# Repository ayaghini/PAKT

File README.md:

# PAKT

## Executive Summary
PAKT is an ESP32-S3-based APRS pocket TNC/tracker built around an SA818 VHF radio,
SGTL5000 audio codec, GPS, and BLE. The MVP now includes both the native PAKT BLE
protocol and KISS-over-BLE so existing APRS software can use the device as a BLE TNC.

The software foundation is substantially in place, and the current bench prototype
has now cleared the core codec and radio bring-up steps:
- firmware includes AX.25/APRS framing, AFSK modulator/demodulator, BLE GATT services,
  KISS-over-BLE, APRS TX scheduling, telemetry payloads, SGTL5000 audio pipeline bring-up,
  staged SA818 bench tests, and SA818 control paths
- the desktop test app and KISS bridge are implemented as reference host tools
- an in-repo iPhone-only SwiftUI app track now exists under `app/ios/`, built against the same native BLE protocol as the desktop client
- host-side software evidence is strong, with current docs recording `364/364` host tests passing
- bench bring-up has confirmed SGTL5000 discovery and headphone output, shared I2C
  visibility for the MAX17048 and M9N, SA818 UART handshake/config, staged PTT/audio tests,
  and short APRS packet TX receipt on a separate receiver

Recent bench work materially improved the RF picture:
- SA818 UART handshake/config recovered and is now responding again on hardware
- staged PTT test and 10-tone TX bench are confirmed working on the current prototype
- APRS packet TX is now bench-proven again on the current hardware state, with packets
  received externally during the restored full test flow
- RX analog/audio activity reaches the demodulator and now has stronger instrumentation
- RX debug now includes PSRAM-backed WAV export, selectable bench stages, selectable
  sample-path conditioning, and a `16 kHz` capture mode
- a separate quiet-capture firmware profile now supports repeated `30 s` low-noise
  captures with a countdown and framed binary export suitable for handoff analysis
- on-device APRS RX is now proven on hardware after fixing a half-rate I2S capture bug
  and reducing Stage C SA818 receive volume; the prototype now decodes APRS frames on-device
- the APRS message-ack path is now wired into `TxScheduler`, so on-air APRS acks
  can complete the firmware message FSM instead of always timing out
- the GPS path now prefers the shared Feather I2C/STEMMA bus (`u-blox M9N @ 0x42`)
  with `UART2` (`GPIO17/GPIO18`, `38400` baud) retained as a fallback; raw NMEA
  traffic is now logged/published even before a valid fix
- GPS over the shared Feather I2C/STEMMA bus is now working on the current
  prototype, including live telemetry delivery to the app; this path should now
  be treated as the default GPS integration baseline rather than an open bring-up item

The project is not MVP-complete yet because hardware validation still gates the milestone:
- BLE security and PTT fail-safe validation on hardware
- SA818 deviation and on-air receive/transmit calibration
- trusted Bell 202 source validation and on-device APRS RX proof
- third-party KISS client validation

## Project Status At A Glance

| Area | Status | Notes |
|---|---|---|
| Core firmware architecture | `strong` | AX.25/APRS, AFSK, BLE, KISS-over-BLE, scheduling, and host tooling are implemented |
| Bench bring-up | `in progress` | I2C, codec bring-up, SA818 UART/config, PTT, staged TX audio, and APRS TX bench are working |
| APRS TX over RF | `proven on current prototype` | tone sequence and APRS packets were heard/received again after SA818 recovery on 2026-03-21 |
| APRS RX over RF | `proven on current prototype` | quiet-profile RX now decodes APRS on-device after fixing the half-rate capture bug and reducing Stage C volume |
| BLE/KISS hardware validation | `pending` | software-complete enough for hardware validation |
| GPS over shared I2C | `proven on current prototype` | `u-blox M9N @ 0x42` is detected after startup, hot-switches to I2C/DDC, and publishes live telemetry to the app |
| MVP milestone | `open` | blocked by BLE safety validation, radio calibration/repeatability, and remaining hardware gates

## Progress Summary
- Software stack is largely implemented and test-backed.
- Prototype hardware can boot the codec/radio path, recover SA818 control, transmit APRS packets over RF, and now decode APRS on-device.
- Main firmware is now in production mode by default: recorder/export bench stages are disabled on boot while the continuous APRS RX path remains active.
- Demodulator instrumentation now exposes RX peak, flag, FCS-reject, and decode counters during bench work.
- Bench stages are now selectable through [bench_profile_config.h](/Users/macmini4/Desktop/PAKT/firmware/main/bench_profile_config.h), so debug sessions can run only the needed benches/stages instead of the full boot-time sequence.
- Full RX recorder/export now works through PSRAM-backed WAV capture, and the quiet profile can export captured demod-input audio through a framed binary serial stream for offline reconstruction.
- A real RX blocker was found and fixed: the audio pipeline was unpacking only half of each 2048-byte I2S read, effectively feeding the demodulator at `8 kHz` while configured for `16 kHz`.
- After fixing that bug and lowering quiet-profile Stage C SA818 volume from `8` to `4`, the device decoded multiple on-air APRS frames in the same `30 s` window.
- GPS parsing is no longer a stub: `gps_task` now reads the M9N over the shared I2C bus when present, falls back to UART if needed, and publishes BLE GPS telemetry even in the no-fix state.
- GPS over the shared Feather I2C/STEMMA bus is now confirmed working in the current hardware setup, and live GPS data is reaching the app.
- APRS ack handling is no longer a dead end: received APRS acks can now call `ctx.notify_ack()` and complete the message FSM in firmware.
- The RX path is now also configurable at the firmware level for:
  - `8 kHz` or `16 kHz` audio rate
  - left/right/average/stronger channel selection
  - stereo-slot swap
  - sample byte swap
  - firmware DC blocking
- The current best debugging workflow is the separate quiet-capture profile.
- The repo now distinguishes clearly between:
  - audio-path alive
  - packet TX proven
  - on-device APRS RX now proven on the corrected quiet profile

## Immediate Next Steps
1. Validate BLE encrypted+bonded write enforcement and PTT fail-safe behavior on live hardware.
2. Verify the newly wired APRS ack path end-to-end with real on-air message acknowledgements.
3. Validate native BLE + KISS-over-BLE behavior on hardware, including reconnect and at least one real client path.
4. Bring up the iPhone app against the same firmware build: connect, view APRS RX/GPS/status, send TX requests, change radio settings, and enable the BLE debug stream.
5. Keep the shared-I2C GPS path as the default baseline and only use UART fallback for alternate wiring or recovery.

## Bench Profile
- Bench/debug stage selection is controlled in [bench_profile_config.h](/Users/macmini4/Desktop/PAKT/firmware/main/bench_profile_config.h).
- Current toggles allow independent enable/disable of:
  - `audio_bench`
  - `sa818_bench`
  - `aprs_bench`
  - APRS Stage 0 loopback
  - APRS Stage A TX burst
  - APRS Stage B RX gain sweep
  - APRS PCM snapshot dump
  - APRS Stage C full RX recorder/export
- Stage C also has a selectable ADC gain step so targeted RX captures can be taken at the most useful receive setting.
- The same file now controls the audio debug sample rate and RX sample interpretation path.

## Current Status
- Phase: prototype hardware bring-up in progress, with packet TX, on-device APRS RX, and shared-I2C GPS telemetry now proven on the current prototype; remaining work is calibration, repeatability, app validation, and safety validation
- Firmware build flow: ESP-IDF with `idf.py`
- Host test flow: raw CMake only for `firmware/test_host`
- Canonical wire-format source: `docs/aprs_mvp_docs/payload_contracts.md`
- Canonical implementation/risk ledger: `docs/aprs_mvp_docs/agent_bootstrap/audit.md`

## Bench-Proven Baseline
- Feather target: Adafruit ESP32-S3 Feather `4 MB flash / 2 MB PSRAM`
- Shared I2C bus: `SGTL5000 @ 0x0A`, `MAX17048 @ 0x36`, `u-blox M9N @ 0x42`
- Audio bring-up rule: enable `SYS_MCLK` before SGTL5000 I2C init
- Verified audio wiring:
  - `GPIO3` `I2C_SDA`
  - `GPIO4` `I2C_SCL`
  - `GPIO8` `I2S_BCLK`
  - `GPIO15` `I2S_WS`
  - `GPIO12` `I2S_DOUT`
  - `GPIO10` `I2S_DIN`
  - `GPIO14` `I2S_MCLK`
- Verified radio control wiring:
  - `GPIO13` `SA818_RX_CTRL`
  - `GPIO9` `SA818_TX_STAT`
  - `GPIO11` `SA818_PTT`
- Restored and re-verified on 2026-03-21:
  - `AT+DMOCONNECT` handshake passes
  - `AT+DMOSETGROUP` frequency config passes
  - staged PTT test passes
  - 10-tone TX bench is audible on a receiver
  - APRS packet TX is received externally
- Bench modules now in the firmware tree:
  - `firmware/main/audio_bench_test/`
  - `firmware/main/sa818_bench_test/`

## Next Steps
- Measure TX deviation and formalize the corrected RX baseline in the bench docs
- Re-run APRS RX across multiple sessions to confirm repeatable decode margin on the corrected quiet profile
- If needed, tune SGTL5000 input/gain/sample interpretation using the new sample-path debug controls, but the core on-device RX proof now exists
- Measure and record SA818 TX deviation with the actual `LINE_OUT -> AF_IN` attenuation in place
- Validate BLE security enforcement and PTT watchdog behavior on the live hardware stack
- Freeze the harness values into the PCB-facing docs once AF levels, deviation, and PTT topology are measured

## Start Here
- `docs/README.md`
- `docs/aprs_mvp_docs/README.md`
- `docs/aprs_mvp_docs/agent_bootstrap/README.md`
- `docs/aprs_mvp_docs/agent_bootstrap/implementation_steps_mvp.md`
- `docs/aprs_mvp_docs/agent_bootstrap/gate_pass_matrix.md`
- `docs/aprs_mvp_docs/agent_bootstrap/audit.md`
- `docs/aprs_mvp_docs/docs/02_mvp_scope.md`
- `docs/aprs_mvp_docs/docs/05_ble_gatt_spec.md`
- `docs/aprs_mvp_docs/docs/19_ble_integration_reference.md`
- `docs/aprs_mvp_docs/docs/16_kiss_over_ble_spec.md`
- `docs/aprs_mvp_docs/payload_contracts.md`
- `docs/dev_setup.md`
- `docs/bench_bringup_checklist.md`
- `hardware/prototyping_wiring.md`
- `hardware/prototype_breakout_wiring_plan.md`

## Repository Layout
- `docs/`: unified documentation home
- `firmware/`: ESP-IDF firmware, host tests, and embedded integration code
- `app/desktop_test/`: desktop BLE reference client and KISS bridge/harness
- `docs/aprs_mvp_docs/docs/`: product, architecture, protocol, firmware, test, and risk docs
- `docs/aprs_mvp_docs/agent_bootstrap/`: low-token onboarding pack, implementation sequence, gates, and audit log
- `docs/aprs_mvp_docs/hardware/`: hardware interface notes and placeholder BOM
- `docs/hardware/`: hardware source library, CAD asset tracking, and reference links
- `docs/dev_setup.md` + `docs/bench_bringup_checklist.md`: operator/developer companion docs
- `hardware/`: practical prototyping wiring and hardware rationale
- `handoff/agent_integration_package/`: external-agent handoff package for host-software integration work

## Working Rules
- Use ESP-IDF `idf.py` for firmware builds; do not use raw CMake as the direct firmware entrypoint.
- Use raw CMake only for pure-software host tests under `firmware/test_host`.
- Keep `docs/aprs_mvp_docs/docs/05_ble_gatt_spec.md`,
- `docs/aprs_mvp_docs/docs/19_ble_integration_reference.md`,
- `docs/aprs_mvp_docs/agent_bootstrap/ble_protocol_quickref.md`,
  `docs/aprs_mvp_docs/docs/16_kiss_over_ble_spec.md`, and
  `docs/aprs_mvp_docs/payload_contracts.md` aligned with the implementation.
- If BLE UUIDs, payload fields, command semantics, chunking, or client behavior changes,
  update all relevant protocol docs in the same change so the desktop app, iPhone app,
  firmware, and future integrations do not drift.
- Prefer `firmware/main/main.cpp` and the component implementations as the source of truth for what is actually wired versus still hardware-gated.

## Build Directories
- `firmware/build_*` are the intended build output directories for the firmware project.
- Repo-root `build_feather_s3/` is also an ESP-IDF-generated build tree for the same `firmware/` project, not a second source tree.
- The metadata inside both `build_feather_s3/project_description.json` and `firmware/build_feather_s3/project_description.json` points back to `firmware/`; the difference is only the chosen build output path.

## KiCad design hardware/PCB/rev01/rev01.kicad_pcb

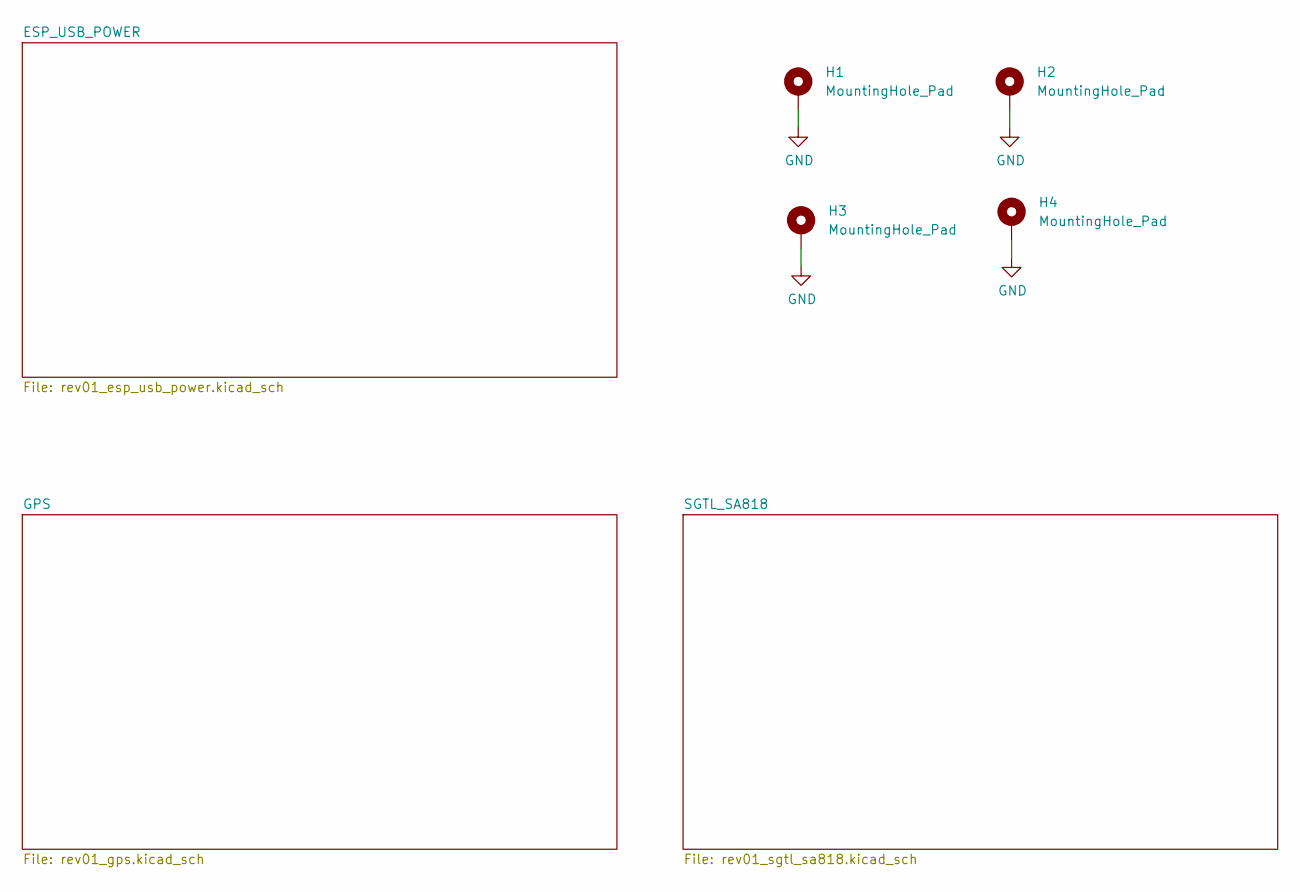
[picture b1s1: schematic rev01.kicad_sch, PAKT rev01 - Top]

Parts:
H1, H2, H3, H4: MountingHole_Pad; MountingHole_3.2mm_M3_Pad

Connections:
GND: H1.1, H2.1, H3.1, H4.1; also elsewhere on the board

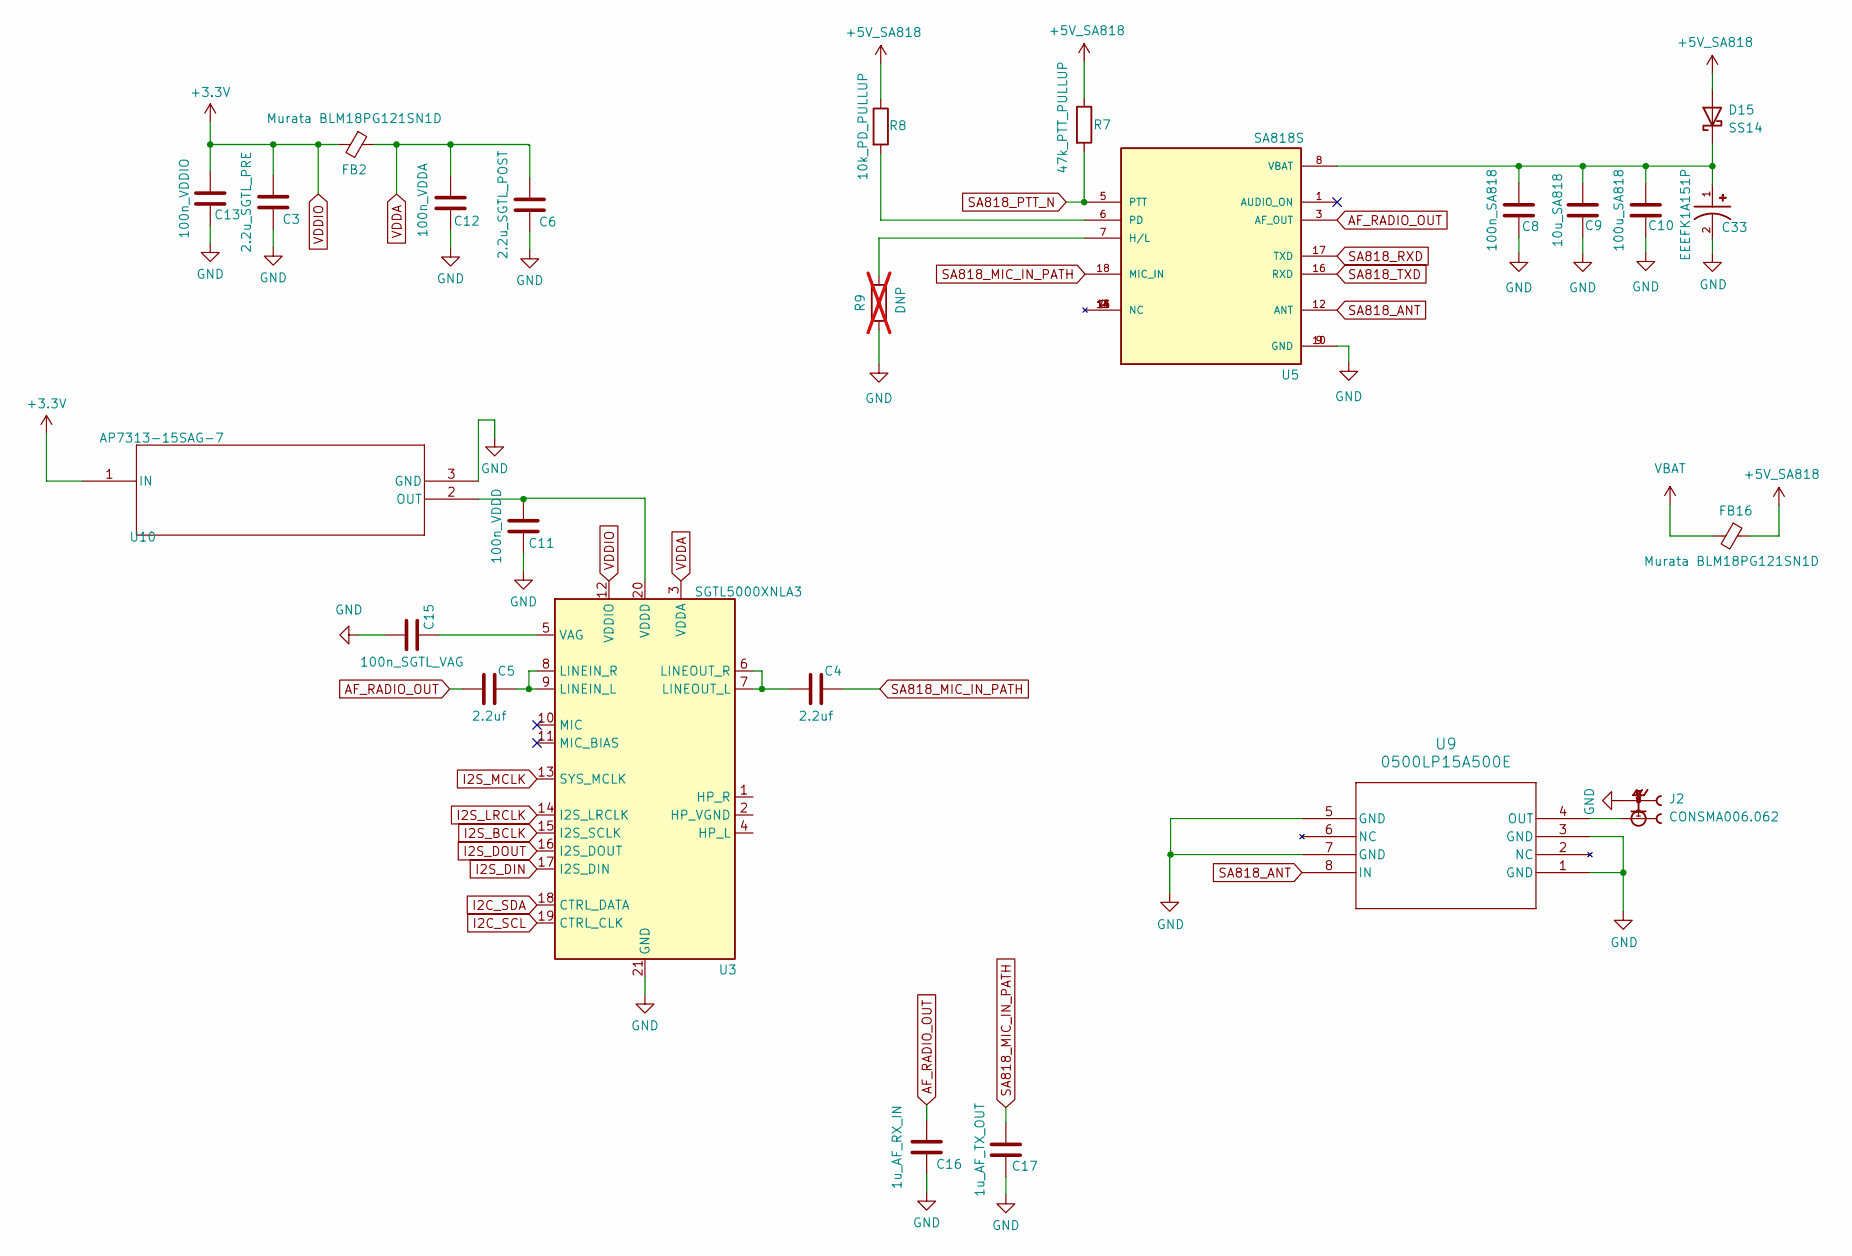
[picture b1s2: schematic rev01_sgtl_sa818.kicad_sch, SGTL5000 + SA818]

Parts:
C3: 2.2u_SGTL_PRE; C_0603_1608Metric
C4, C5: 2.2uf; C_0603_1608Metric
C6: 2.2u_SGTL_POST; C_0603_1608Metric
C8: 100n_SA818; C_0603_1608Metric
C9: 10u_SA818; C_0805_2012Metric
C10: 100u_SA818; C_1206_3216Metric
C11: 100n_VDDD; C_0603_1608Metric
C12: 100n_VDDA; C_0603_1608Metric
C13: 100n_VDDIO; C_0603_1608Metric
C15: 100n_SGTL_VAG; C_0603_1608Metric
C16: 1u_AF_RX_IN; C_0603_1608Metric
C17: 1u_AF_TX_OUT; C_0603_1608Metric
C33: EEEFK1A151P; CAP_EEEFK1A151P; PARTREV 10-Oct-19
D15: SS14; D_SMA; MPN SS14
FB2, FB16: Murata BLM18PG121SN1D; R_0603_1608Metric; MPN BLM18PG121SN1D
J2: CONSMA006.062; SMA_Amphenol_132134-14_Vertical_P5; PARTREV B
R7: 47k_PTT_PULLUP; R_0603_1608Metric
R8: 10k_PD_PULLUP; R_0603_1608Metric
R9: DNP; R_0603_1608Metric; not fitted
U3: SGTL5000XNLA3; HUQFN20_SOT1628-1_NXP
U5: SA818S; XCVR_SA818S
U9: 0500LP15A500E; 0500LP15A500E_JOT; MPN 0500LP15A500E
U10: AP7313-15SAG-7; AP7313_15SAG_7

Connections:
+5V_SA818: D15.2 (A), FB16.1, R7.1, R8.1
AF_RADIO_OUT: C5.1, C16.1, U5.3 (AF_OUT)
GND: C3.2, C6.2, C8.2, C9.2, C10.2, C11.2, C12.2, C13.2, C15.1, C16.2, C17.2, C33.2, J2.2, J2.3, J2.4, J2.5, R9.1, U3.21 (GND), U5.9 (GND), U5.10 (GND), U9.1 (GND), U9.3 (GND), U9.5 (GND), U9.7 (GND), U10.3 (GND); also elsewhere on the board
I2C_SCL: U3.19 (CTRL_CLK); also elsewhere on the board
I2C_SDA: U3.18 (CTRL_DATA); also elsewhere on the board
I2S_BCLK: U3.15 (I2S_SCLK); also elsewhere on the board
I2S_DIN: U3.17 (I2S_DIN); also elsewhere on the board
I2S_DOUT: U3.16 (I2S_DOUT); also elsewhere on the board
I2S_LRCLK: U3.14 (I2S_LRCLK); also elsewhere on the board
I2S_MCLK: U3.13 (SYS_MCLK); also elsewhere on the board
unnamed: C8.1, C9.1, C10.1, C33.1, D15.1 (K), U5.8 (VBAT)
unnamed: C5.2, U3.8 (LINEIN_R), U3.9 (LINEIN_L)
unnamed: C4.1, U3.6 (LINEOUT_R), U3.7 (LINEOUT_L)
unnamed: C15.2, U3.5 (VAG)
unnamed: R9.2, U5.7 (H/L)
unnamed: R8.2, U5.6 (PD)
unnamed: J2.1, U9.4 (OUT)
unnamed: C11.1, U3.20 (VDDD), U10.2 (OUT)
SA818_ANT: U5.12 (ANT), U9.8 (IN)
SA818_MIC_IN_PATH: C4.2, C17.1, U5.18 (MIC_IN)
SA818_PTT_N: R7.2, U5.5 (PTT); also elsewhere on the board
SA818_RXD: U5.17 (TXD); also elsewhere on the board
SA818_TXD: U5.16 (RXD); also elsewhere on the board
VBAT: FB16.2; also elsewhere on the board
VDDA: C6.1, C12.1, FB2.1, U3.3 (VDDA)
VDDIO: C3.1, C13.1, FB2.2, U3.12 (VDDIO), U10.1 (IN); also elsewhere on the board

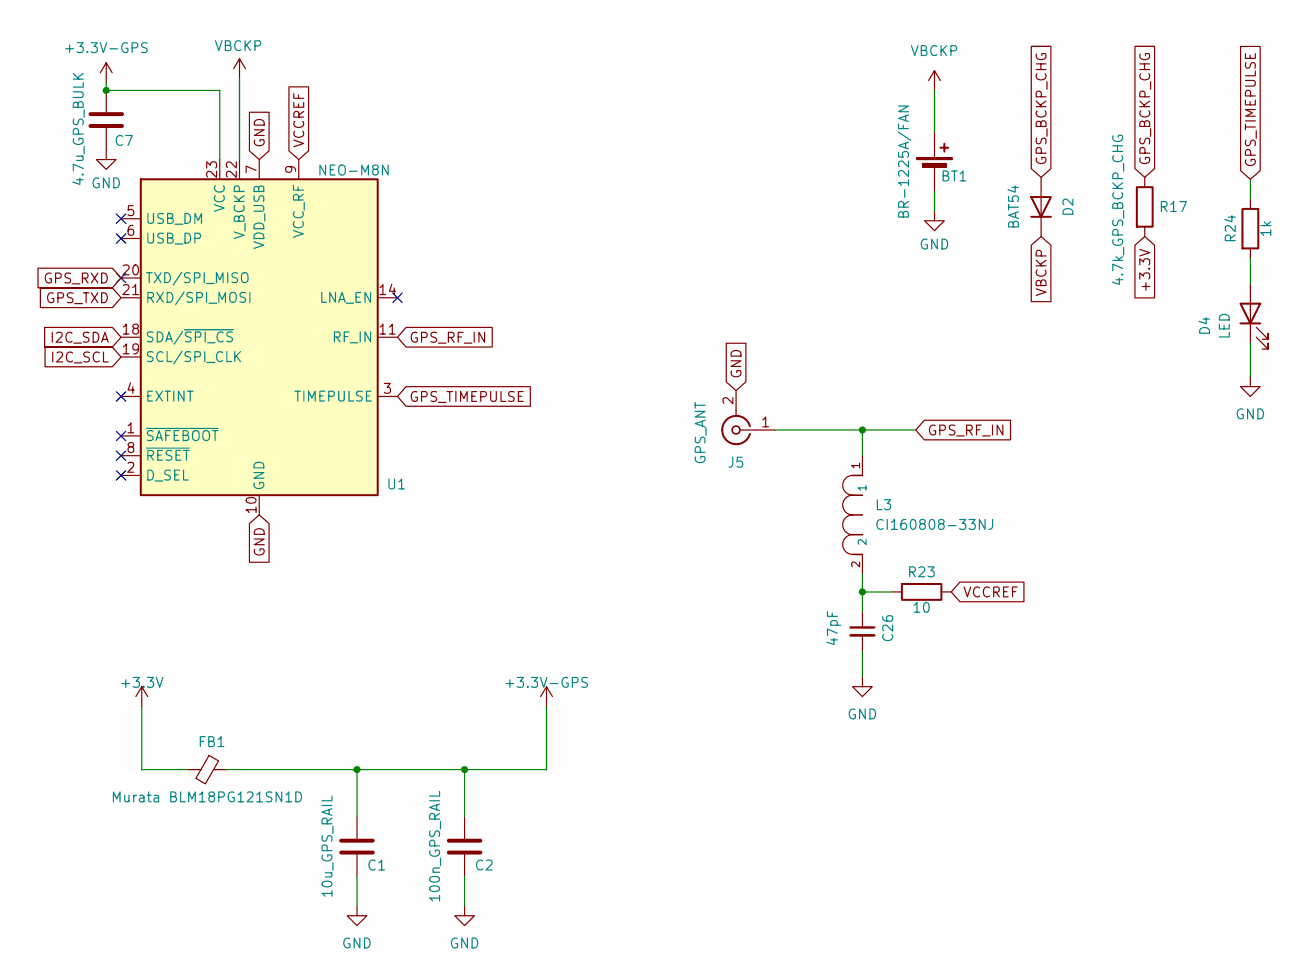
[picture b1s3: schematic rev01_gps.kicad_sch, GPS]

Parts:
BT1: BR-1225A/FAN; BatteryHolder_Keystone_3000_1x12mm
C1: 10u_GPS_RAIL; C_0805_2012Metric
C2: 100n_GPS_RAIL; C_0603_1608Metric
C7: 4.7u_GPS_BULK; C_0805_2012Metric
C26: 47pF; C_0402_1005Metric
D2: BAT54; D_SOD-323
D4: LED; LED_0603_1608Metric
FB1: Murata BLM18PG121SN1D; R_0603_1608Metric; MPN BLM18PG121SN1D
J5: GPS_ANT; U.FL_Hirose_U.FL-R-SMT-1_Vertical
L3: CI160808-33NJ; L_0603_1608Metric; TOLERANCE ±5 %; MPN CI160808-33NJ
R17: 4.7k_GPS_BCKP_CHG; R_0603_1608Metric
R23: 10; R_0603_1608Metric
R24: 1k; R_0603_1608Metric
U1: NEO-M8N; ublox_NEO

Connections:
+3.3V-GPS: C1.1, C2.1, C7.1, FB1.1, U1.23 (VCC)
GND: BT1.2 (-), C1.2, C2.2, C7.2, C26.2, D4.1 (K), J5.2 (Ext), U1.7 (VDD_USB), U1.10 (GND), U1.12 (GND), U1.13 (GND), U1.24 (GND); also elsewhere on the board
GPS_BCKP_CHG: D2.2 (A), R17.1
GPS_RF_IN: J5.1 (In), L3.1, U1.11 (RF_IN)
GPS_RXD: U1.20 (TXD/SPI_MISO); also elsewhere on the board
GPS_TIMEPULSE: R24.1, U1.3 (TIMEPULSE)
GPS_TXD: U1.21 (RXD/SPI_MOSI); also elsewhere on the board
I2C_SCL: U1.19 (SCL/SPI_CLK); also elsewhere on the board
I2C_SDA: U1.18 (SDA/~SPI_CS); also elsewhere on the board
unnamed: C26.1, L3.2, R23.2
unnamed: D4.2 (A), R24.2
VBCKP: BT1.1 (+), D2.1 (K), U1.22 (V_BCKP)
VCCREF: R23.1, U1.9 (VCC_RF)
VDDIO: FB1.2, R17.2; also elsewhere on the board

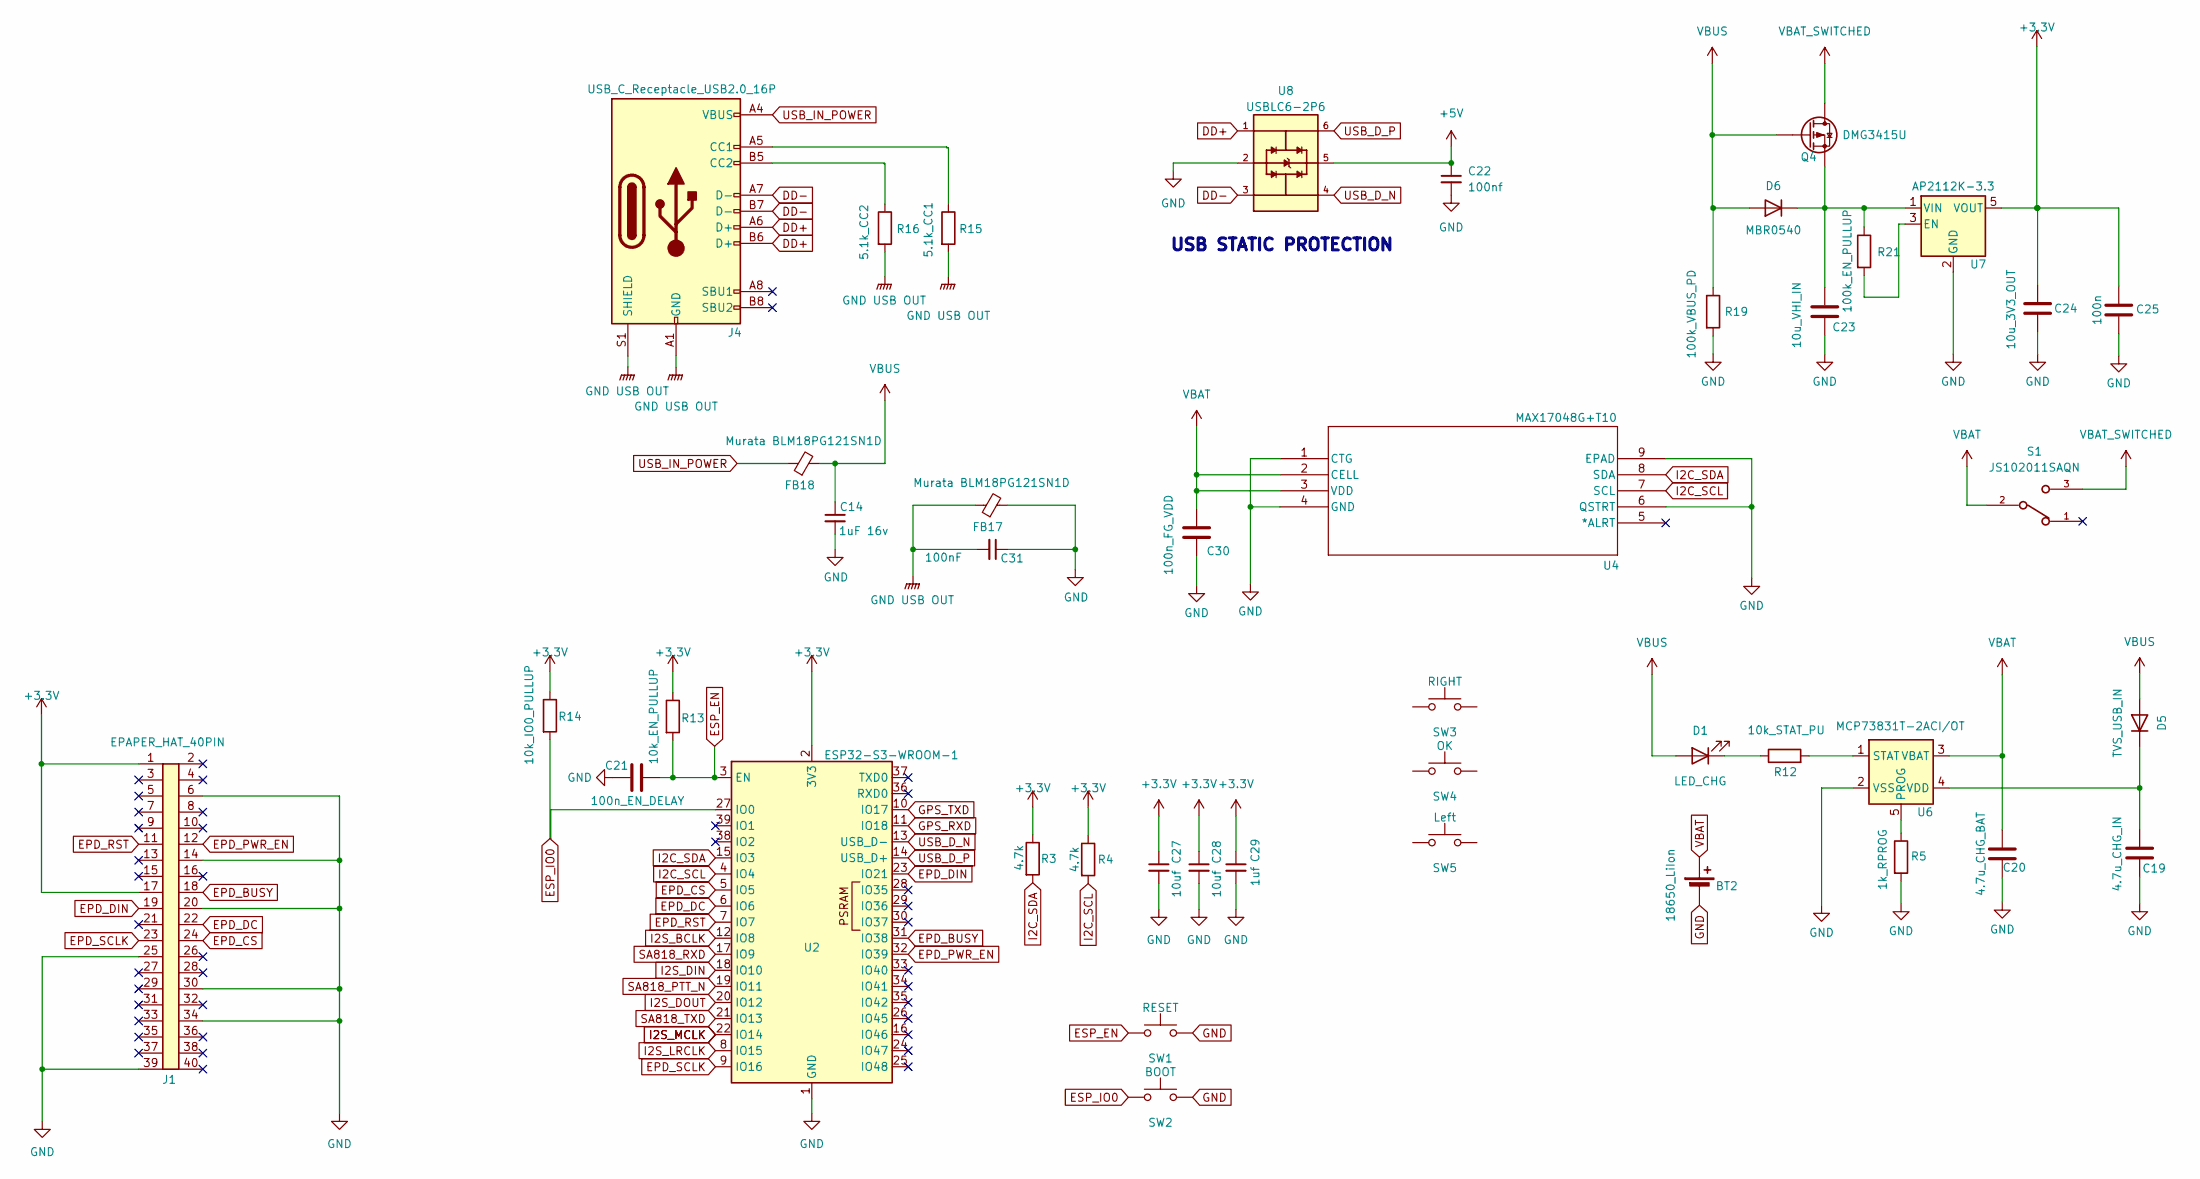
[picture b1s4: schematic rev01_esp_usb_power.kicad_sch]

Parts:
BT2: 18650_LiIon; BatteryHolder_Keystone_1042_1x18650
C14: 1uF 16v; C_0603_1608Metric; MPN CL05A105KA5NQNC; LCSC C52923
C19: 4.7u_CHG_IN; C_0805_2012Metric
C20: 4.7u_CHG_BAT; C_0805_2012Metric
C21: 100n_EN_DELAY; C_0603_1608Metric
C22: 100nf; C_0603_1608Metric
C23: 10u_VHI_IN; C_0805_2012Metric
C24: 10u_3V3_OUT; C_0805_2012Metric
C25: 100n; C_0603_1608Metric
C27, C28: 10uf; C_0805_2012Metric
C29: 1uf; C_0805_2012Metric
C30: 100n_FG_VDD; C_0603_1608Metric
C31: 100nF; C_0603_1608Metric; MPN CL05B104KO5NNNC; LCSC C1525
D1: LED_CHG; LED_0603_1608Metric
D5: TVS_USB_IN; D_SOD-323
D6: MBR0540; D_SOD-123
FB17, FB18: Murata BLM18PG121SN1D; R_0603_1608Metric; MPN BLM18PG121SN1D
J1: EPAPER_HAT_40PIN; PinSocket_2x20_P2.54mm_Vertical; MPN PPTC202LFBN-RC
J4: USB_C_Receptacle_USB2.0_16P; USB_C_Receptacle_GCT_USB4105-xx-A_16P_TopMnt_Horizontal
Q4: DMG3415U; SOT-23_GSD
R3, R4: 4.7k; R_0603_1608Metric
R5: 1k_RPROG; R_0603_1608Metric
R12: 10k_STAT_PU; R_0603_1608Metric
R13: 10k_EN_PULLUP; R_0603_1608Metric
R14: 10k_IO0_PULLUP; R_0603_1608Metric
R15: 5.1k_CC1; R_0603_1608Metric
R16: 5.1k_CC2; R_0603_1608Metric
R19: 100k_VBUS_PD; R_0603_1608Metric
R21: 100k_EN_PULLUP; R_0603_1608Metric
S1: JS102011SAQN; SW_JS102011SAQN
SW1: RESET; SW_SPST_TL3342
SW2: BOOT; SW_SPST_TL3342
SW3: RIGHT; SW_SPST_TL3342
SW4: OK; SW_SPST_TL3342
SW5: Left; SW_SPST_TL3342
U2: ESP32-S3-WROOM-1
U4: MAX17048G+T10; MAX17048
U6: MCP73831T-2ACI/OT; SOT-23-5
U7: AP2112K-3.3; SOT-23-5
U8: USBLC6-2P6; SOT-666; PARTREV 5

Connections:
+5V: C22.1, U8.5
DD+: J4.A6 (D+), J4.B6 (D+), U8.1
DD-: J4.A7 (D-), J4.B7 (D-), U8.3
EPD_BUSY: J1.18, U2.31 (IO38)
EPD_CS: J1.24, U2.5 (IO5)
EPD_DC: J1.22, U2.6 (IO6)
EPD_DIN: J1.19, U2.23 (IO21)
EPD_PWR_EN: J1.12, U2.32 (IO39)
EPD_RST: J1.11, U2.7 (IO7)
EPD_SCLK: J1.23, U2.9 (IO16)
ESP_EN: C21.2, R13.2, SW1.1, U2.3 (EN)
ESP_IO0: R14.2, SW2.1, U2.27 (IO0)
GND: BT2.2 (-), C14.2, C19.2, C20.2, C21.1, C22.2, C23.2, C24.2, C25.2, C27.2, C28.2, C29.2, C30.2, C31.1, FB17.2, J1.6, J1.14, J1.20, J1.25, J1.30, J1.34, J1.39, R5.2, R19.2, SW1.2, SW2.2, U2.1 (GND), U2.40 (GND), U2.41 (GND), U4.1 (CTG), U4.4 (GND), U4.6 (QSTRT), U4.9 (EPAD), U6.2 (VSS), U7.2 (GND), U8.2; also elsewhere on the board
GND USB OUT: C31.2, FB17.1, J4.A1 (GND), J4.A12 (GND), J4.B1 (GND), J4.B12 (GND), J4.S1 (SHIELD), R15.2, R16.2
GPS_RXD: U2.11 (IO18); also elsewhere on the board
GPS_TXD: U2.10 (IO17); also elsewhere on the board
I2C_SCL: R4.2, U2.4 (IO4), U4.7 (SCL); also elsewhere on the board
I2C_SDA: R3.2, U2.15 (IO3), U4.8 (SDA); also elsewhere on the board
I2S_BCLK: U2.12 (IO8); also elsewhere on the board
I2S_DIN: U2.18 (IO10); also elsewhere on the board
I2S_DOUT: U2.20 (IO12); also elsewhere on the board
I2S_LRCLK: U2.8 (IO15); also elsewhere on the board
I2S_MCLK: U2.22 (IO14); also elsewhere on the board
unnamed: D1.1 (K), R12.1
unnamed: C19.1, D5.1 (K), U6.4 (VDD)
unnamed: C23.1, D6.1 (K), Q4.S, R21.1, U7.1 (VIN)
unnamed: J4.A5 (CC1), R15.1
unnamed: J4.B5 (CC2), R16.1
unnamed: R5.1, U6.5 (PROG)
unnamed: R12.2, U6.1 (STAT)
unnamed: R21.2, U7.3 (EN)
SA818_PTT_N: U2.19 (IO11); also elsewhere on the board
SA818_RXD: U2.17 (IO9); also elsewhere on the board
SA818_TXD: U2.21 (IO13); also elsewhere on the board
USB_D_N: U2.13 (USB_D-), U8.4
USB_D_P: U2.14 (USB_D+), U8.6
USB_IN_POWER: FB18.1, J4.A4 (VBUS), J4.A9 (VBUS), J4.B4 (VBUS), J4.B9 (VBUS)
VBAT: BT2.1 (+), C20.1, C30.1, S1.2, U4.2 (CELL), U4.3 (VDD), U6.3 (VBAT); also elsewhere on the board
VBAT_SWITCHED: Q4.D, S1.3
VBUS: C14.1, D1.2 (A), D5.2 (A), D6.2 (A), FB18.2, Q4.G, R19.1
VDDIO: C24.1, C25.1, C27.1, C28.1, C29.1, J1.1, J1.17, R3.1, R4.1, R13.1, R14.1, U2.2 (3V3), U7.5 (VOUT); also elsewhere on the board

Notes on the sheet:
USB STATIC PROTECTION

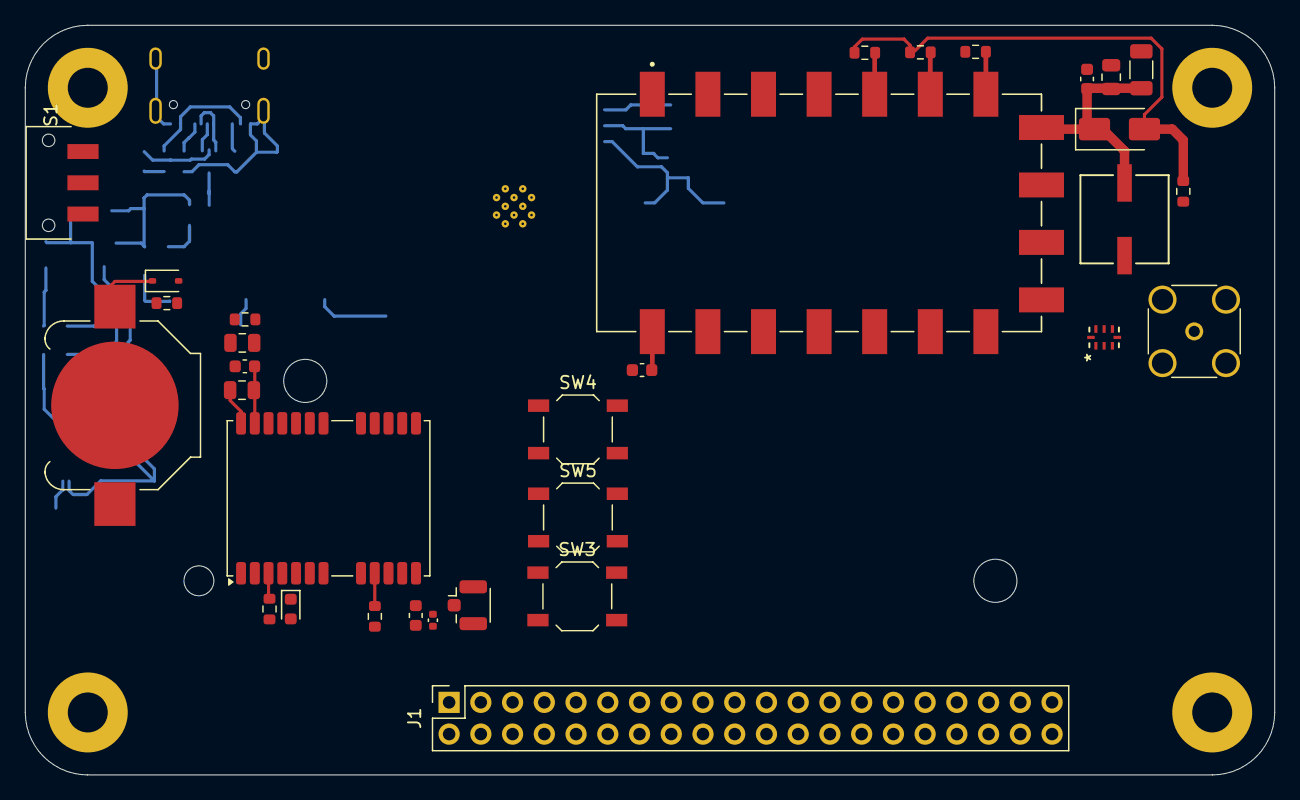
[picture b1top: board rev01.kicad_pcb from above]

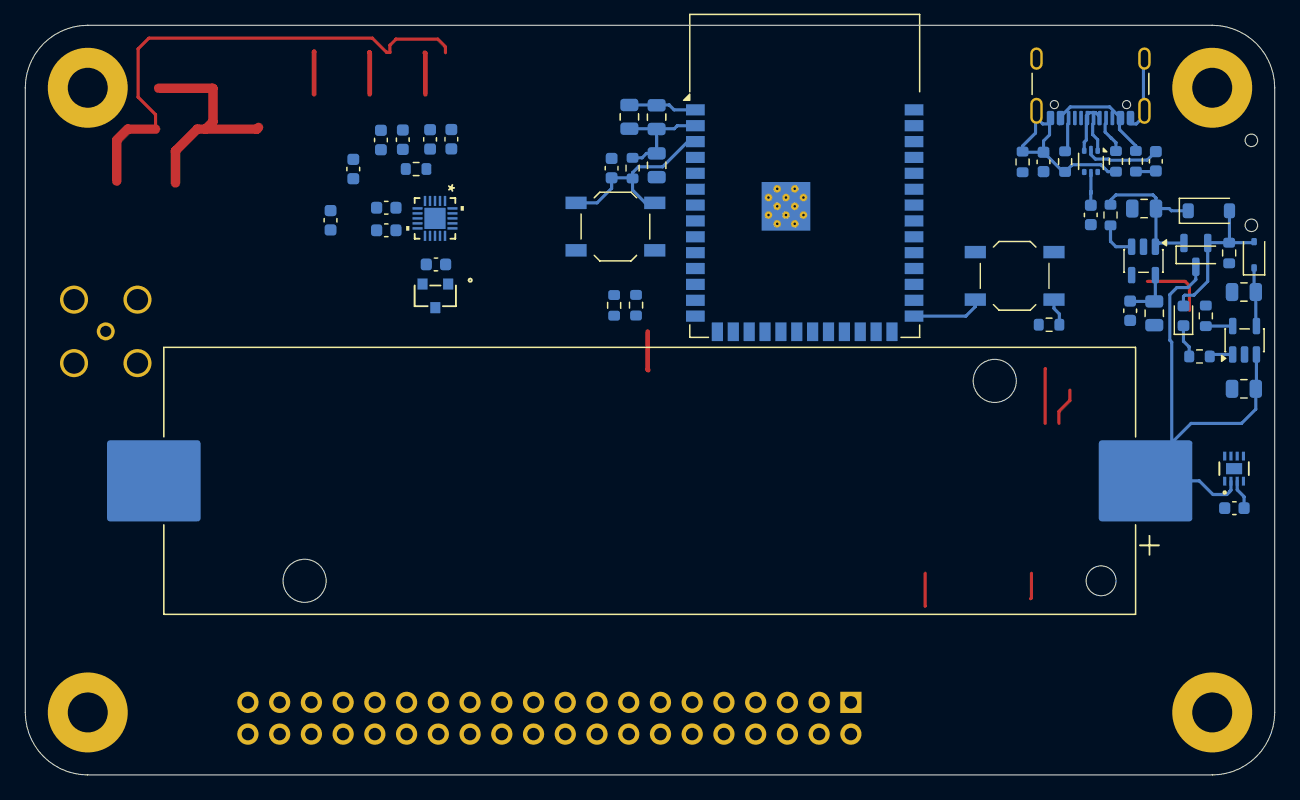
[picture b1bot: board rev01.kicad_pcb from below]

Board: 2 copper layers, 100.0 x 60.0 mm, 86 parts (50 on the bottom side), 62 nets.

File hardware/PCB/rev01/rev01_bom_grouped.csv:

"Quantity","Value","Footprint","MPN","Manufacturer","DNP","References","Notes"
"1","0500LP15A500E","PAKT_Local_Fp:Johanson_0500LP15A500E_P8","0500LP15A500E","Johanson Technology","no","U9","SA818 RF low-pass filter"
"1","0R_QSTRT_GND","Resistor_SMD:R_0603_1608Metric","RC0603JR-070RL","Yageo","no","R11","Jumper 0603"
"1","10","Resistor_SMD:R_0603_1608Metric","RC0603FR-0710RL","Yageo","no","R23","1% 0603"
"1","100k_EN_PULLUP","Resistor_SMD:R_0603_1608Metric","RC0603FR-07100KL","Yageo","no","R21","1% 0603"
"1","100k_VBUS_PD","Resistor_SMD:R_0603_1608Metric","RC0603FR-07100KL","Yageo","no","R19","1% 0603"
"1","100n","Capacitor_SMD:C_0603_1608Metric","CL10B104KB8NNNC","Samsung","no","C25","100nF 50V X7R 0603"
"1","100n_EN_DELAY","Capacitor_SMD:C_0603_1608Metric","CL10B104KB8NNNC","Samsung","no","C21","100nF 50V X7R 0603"
"1","100n_FG_VDD","Capacitor_SMD:C_0603_1608Metric","CL10B104KB8NNNC","Samsung","no","C18","100nF 50V X7R 0603"
"1","100n_GPS_RAIL","Capacitor_SMD:C_0603_1608Metric","CL10B104KB8NNNC","Samsung","no","C2","100nF 50V X7R 0603"
"1","100n_SA818","Capacitor_SMD:C_0603_1608Metric","CL10B104KB8NNNC","Samsung","no","C8","100nF 50V X7R 0603"
"1","100n_SGTL_VAG","Capacitor_SMD:C_0603_1608Metric","CL10B104KB8NNNC","Samsung","no","C15","100nF 50V X7R 0603"
"1","100n_VDDA","Capacitor_SMD:C_0603_1608Metric","CL10B104KB8NNNC","Samsung","no","C12","100nF 50V X7R 0603"
"1","100n_VDDD","Capacitor_SMD:C_0603_1608Metric","CL10B104KB8NNNC","Samsung","no","C11","100nF 50V X7R 0603"
"1","100n_VDDIO","Capacitor_SMD:C_0603_1608Metric","CL10B104KB8NNNC","Samsung","no","C13","100nF 50V X7R 0603"
"2","100nf","Capacitor_SMD:C_0603_1608Metric","CL10B104KB8NNNC","Samsung","no","C22, C31","100nF 50V X7R 0603"
"1","100u_SA818","Capacitor_SMD:C_1206_3216Metric","GRM31CR60J107ME39L","Murata","no","C10","100uF 6.3V X5R 1206 (verify derating)"
"1","10k_ALRT_PU","Resistor_SMD:R_0603_1608Metric","RC0603FR-0710KL","Yageo","no","R10","1% 0603"
"1","10k_EN_PULLUP","Resistor_SMD:R_0603_1608Metric","RC0603FR-0710KL","Yageo","no","R13","1% 0603"
"1","10k_IO0_PULLUP","Resistor_SMD:R_0603_1608Metric","RC0603FR-0710KL","Yageo","no","R14","1% 0603"
"1","10k_PD_PULLUP","Resistor_SMD:R_0603_1608Metric","RC0603FR-0710KL","Yageo","no","R8","1% 0603"
"1","10k_STAT_PU","Resistor_SMD:R_0603_1608Metric","RC0603FR-0710KL","Yageo","no","R12","1% 0603"
"1","10u_3V3_OUT","Capacitor_SMD:C_0805_2012Metric","CL21A106KPFNNNE","Samsung","no","C24","10uF 10V X5R 0805"
"1","10u_GPS_RAIL","Capacitor_SMD:C_0805_2012Metric","CL21A106KPFNNNE","Samsung","no","C1","10uF 10V X5R 0805"
"1","10u_SA818","Capacitor_SMD:C_0805_2012Metric","CL21A106KPFNNNE","Samsung","no","C9","10uF 10V X5R 0805"
"1","10u_VHI_IN","Capacitor_SMD:C_0805_2012Metric","CL21A106KPFNNNE","Samsung","no","C23","10uF 10V X5R 0805"
"2","10uf","Capacitor_SMD:C_0805_2012Metric","CL21A106KPFNNNE","Samsung","no","C27, C28","10uF 10V X5R 0805"
"1","18650_LiIon","Battery:BatteryHolder_Keystone_1042_1x18650","Keystone 1042","Keystone","no","BT2","18650 holder"
"1","1k","Resistor_SMD:R_0603_1608Metric","RC0603FR-071KL","Yageo","no","R24","1% 0603"
"1","1k_RPROG","Resistor_SMD:R_0603_1608Metric","RC0603FR-071KL","Yageo","no","R5","1% 0603"
"1","1u_AF_RX_IN","Capacitor_SMD:C_0603_1608Metric","CL10A105KA8NNNC","Samsung","no","C16","1uF 10V X5R 0603"
"1","1u_AF_TX_OUT","Capacitor_SMD:C_0603_1608Metric","CL10A105KA8NNNC","Samsung","no","C17","1uF 10V X5R 0603"
"1","1uf","Capacitor_SMD:C_0805_2012Metric","CL10A105KA8NNNC","Samsung","no","C29","1uF 10V X5R 0603"
"1","1uF 16v","Capacitor_SMD:C_0603_1608Metric","CL10A105KA8NNNC","Samsung","no","C14","1uF 10V X5R 0603"
"1","2.2u_SGTL_POST","Capacitor_SMD:C_0603_1608Metric","CL10A225KO8NNNC","Samsung","no","C6","2.2uF 16V X5R 0603"
"1","2.2u_SGTL_PRE","Capacitor_SMD:C_0603_1608Metric","CL10A225KO8NNNC","Samsung","no","C3","2.2uF 16V X5R 0603"
"2","2.2uf","Capacitor_SMD:C_0603_1608Metric","CL10A225KO8NNNC","Samsung","no","C4, C5","2.2uF 16V X5R 0603"
"2","4.7k","Resistor_SMD:R_0603_1608Metric","RC0603FR-074K7L","Yageo","no","R3, R4","1% 0603"
"1","4.7k_GPS_BCKP_CHG","Resistor_SMD:R_0603_1608Metric","RC0603FR-074K7L","Yageo","no","R17","1% 0603"
"1","4.7u_CHG_BAT","Capacitor_SMD:C_0805_2012Metric","CL21A475KBQNNNE","Samsung","no","C20","4.7uF 16V X5R 0805"
"1","4.7u_CHG_IN","Capacitor_SMD:C_0805_2012Metric","CL21A475KBQNNNE","Samsung","no","C19","4.7uF 16V X5R 0805"
"1","4.7u_GPS_BULK","Capacitor_SMD:C_0805_2012Metric","CL21A475KBQNNNE","Samsung","no","C7","4.7uF 16V X5R 0805"
"1","47k_PTT_PULLUP","Resistor_SMD:R_0603_1608Metric","RC0603FR-0747KL","Yageo","no","R7","1% 0603"
"1","47pF","Capacitor_SMD:C_0402_1005Metric","CL05C470JB5NNNC","Samsung","no","C26","47pF C0G 0402"
"1","5.1k_CC1","Resistor_SMD:R_0603_1608Metric","RC0603FR-075K1L","Yageo","no","R15","1% 0603"
"1","5.1k_CC2","Resistor_SMD:R_0603_1608Metric","RC0603FR-075K1L","Yageo","no","R16","1% 0603"
"1","AP2112K-3.3","Package_TO_SOT_SMD:SOT-23-5","AP2112K-3.3TRG1","Diodes Inc.","no","U7","3.3V LDO"
"1","BAT54","Diode_SMD:D_SOD-323","BAT54","onsemi","no","D2","Schottky"
"1","BOOT","Button_Switch_SMD:SW_SPST_TL3342","TL3342F160QG","E-Switch","no","SW2","Boot button"
"1","BR-1225A/FAN","Battery:BatteryHolder_Keystone_3000_1x12mm","Keystone 3000","Keystone","no","BT1","CR1225 holder"
"1","CI160808-33NJ","Inductor_SMD:L_0603_1608Metric","CI160808-33NJ","Samsung Electro-Mechanics","no","L3","33nH RF inductor"
"1","CONSMA006.062","PAKT_Local_Fp:SMA_Amphenol_132134-14_Vertical_P5","TBD","TBD","no","J2","Review/Select"
"1","DMG3415U","PAKT_Local_Fp:SOT-23_GSD","DMG3415U-7","Diodes Inc.","no","Q4","P-MOS power path"
"1","DNP","Resistor_SMD:R_0603_1608Metric","DNP","DNP","no","R9","Do not place"
"1","EEEFK1A151P","Capacitor_Tantalum_SMD:CP_EIA-7343-31_Kemet-D","EEEFK1A151P","Panasonic","no","C33","150uF polymer"
"1","ESP32-S3-WROOM-1","PAKT_RF_Module_Fp:ESP32-S3-WROOM-1","ESP32-S3-WROOM-1","Espressif","no","U2","Select flash/PSRAM variant at ordering time"
"1","GPS_ANT","Connector_Coaxial:U.FL_Hirose_U.FL-R-SMT-1_Vertical","U.FL-R-SMT-1(80)","Hirose","no","J5","GPS RF connector"
"1","EPAPER_HAT_40PIN","Connector_PinSocket_2.54mm:PinSocket_2x20_P2.54mm_Vertical","PPTC202LFBN-RC","Sullins","no","J6","2x20 2.54mm female header for Waveshare HAT+; buy: https://www.digikey.com/en/products/detail/sullins-connector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"
"1","LED","LED_SMD:LED_0603_1608Metric","LTST-C190KRKT","Lite-On","no","D4","Red 0603 LED"
"1","LED_CHG","LED_SMD:LED_0603_1608Metric","LTST-C190KGKT","Lite-On","no","D1","Green 0603 LED"
"1","MAX17048G+T10","PAKT_MAX17048_Fp:DFN-8-1EP_3x2mm_P0.5mm_EP1.7x1.4mm","MAX17048G+T10","Analog Devices / Maxim","no","U4","Fuel gauge"
"1","MBR0540","Diode_SMD:D_SOD-123","MBR0540","onsemi","no","D6","Schottky power ORing"
"1","MCP73831T-2ACI/OT","Package_TO_SOT_SMD:SOT-23-5","MCP73831T-2ACI/OT","Microchip","no","U6","Li-ion charger"
"5","Murata BLM18PG121SN1D","Resistor_SMD:R_0603_1608Metric","BLM18PG121SN1D","Murata","no","FB1, FB16, FB17, FB18, FB2","Ferrite bead 120R@100MHz class"
"1","NEO-M8N","PAKT_GPS_Fp:ublox_NEO","NEO-M8N-0","u-blox","no","U1","Can substitute NEO-M8M-0 per layout plan"
"1","RESET","Button_Switch_SMD:SW_SPST_TL3342","TL3342F160QG","E-Switch","no","SW1","Reset button"
"1","SA818S","PAKT_SA818_Fp:XCVR_SA818S","SA818S","NiceRF / Dorji compatible","no","U5","Verify exact vendor footprint"
"1","SGTL5000XNLA3","PAKT_Audio_Fp:QFN-32-1EP_5x5mm_P0.5mm_EP3.6x3.6mm","SGTL5000XNLA3","NXP","no","U3","Audio codec"
"1","SS14","Diode_SMD:D_SMA","SS14","onsemi","no","D15","Schottky"
"1","TVS_USB_IN","Diode_SMD:D_SOD-323","PESD5V0S1UL","Nexperia","no","D5","USB/IO TVS, verify with schematic intent"
"1","USB_C_Receptacle_USB2.0_16P","Connector_USB:USB_C_Receptacle_GCT_USB4105-xx-A_16P_TopMnt_Horizontal","USB4105-GF-A","GCT","no","J4","USB-C receptacle USB2.0"
"1","USBLC6-2P6","Package_TO_SOT_SMD:SOT-666","USBLC6-2P6","STMicroelectronics","no","U8","USB ESD protector"

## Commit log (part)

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2026-02-28 mvp updates
2026-02-28 further mvp progress
2026-02-28 added components datasheet
2026-03-01 hf modem feasibility study initial doc
2026-03-09 mvp prep
2026-03-09 AX25 implementation
2026-03-09 app updates
2026-03-15 app audit updates
2026-03-16 daily updates and software bug fixes
2026-03-17 updates to KISS modem, clean ups and EOD commit
2026-03-20 prototype updates
2026-03-20 RX troubleshooting
2026-03-25 dev up
2026-03-29 gps working, app tx and rx work.
2026-03-29 BLE integration refrence added
2026-04-10 pcb rev01 schematic and nets
2026-04-12 PCB rev01 progress
2026-04-12 pcb progress
2026-04-13 Add SH1106 display smoke test and battery telemetry
2026-05-09 progress on pcb
2026-05-09 added e-paper display
